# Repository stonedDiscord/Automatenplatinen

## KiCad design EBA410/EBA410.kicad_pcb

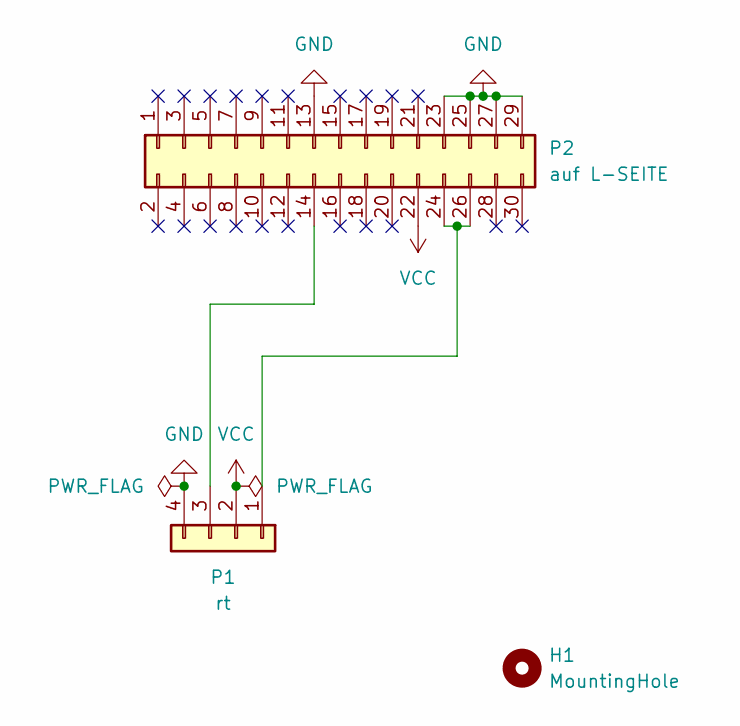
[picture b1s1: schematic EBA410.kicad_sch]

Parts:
H1: MountingHole; MountingHole_3.7mm
P1: rt; PinHeader_1x04_P2.54mm_Horizontal
P2: auf L-SEITE; PinHeader_2x15_P2.54mm_Vertical

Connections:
GND: P1.4, P2.13, P2.23, P2.25, P2.27, P2.29
unnamed: P1.1, P2.24, P2.26
unnamed: P1.3, P2.14
VCC: P1.2, P2.22

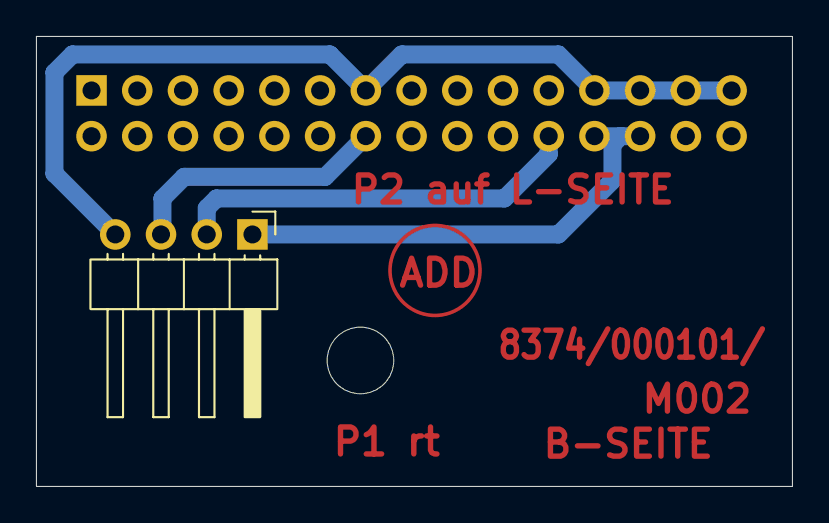
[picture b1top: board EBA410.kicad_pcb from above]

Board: 2 copper layers, 42.0 x 25.0 mm, 3 parts (1 on the bottom side), 4 nets.

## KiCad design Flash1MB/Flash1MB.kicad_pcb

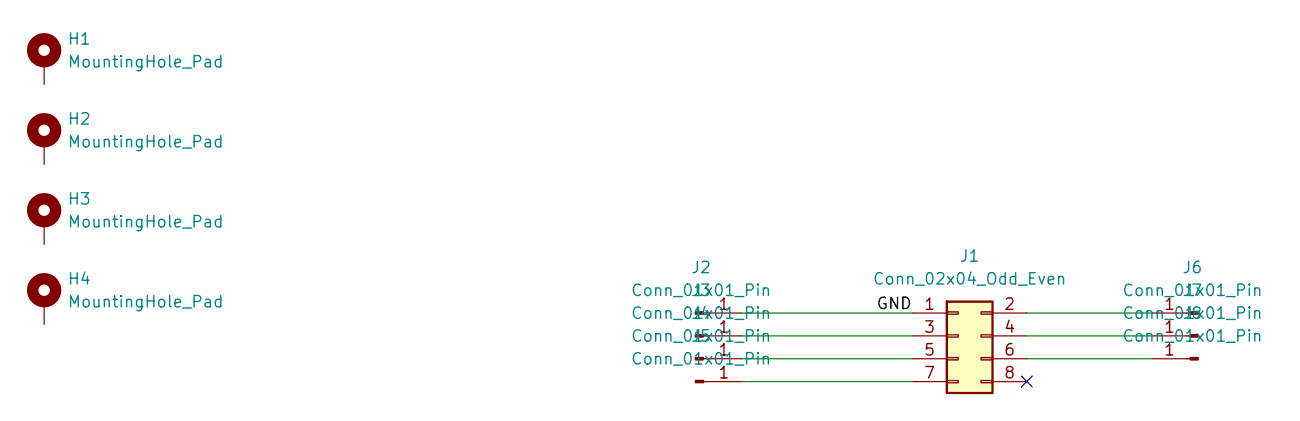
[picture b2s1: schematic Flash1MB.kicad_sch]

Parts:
H1, H2, H3, H4: MountingHole_Pad; MountingHole_2.2mm_M2_DIN965_Pad
J1: Conn_02x04_Odd_Even; PinHeader_2x04_P2.54mm_Vertical
J2, J3, J4, J5, J6, J7, J8: Conn_01x01_Pin; PinHeader_1x01_P2.54mm_Vertical

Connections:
/GND: J1.1, J2.1
unnamed: J1.2, J6.1
unnamed: J1.3, J3.1
unnamed: J1.4, J7.1
unnamed: J1.5, J4.1
unnamed: J1.6, J8.1
unnamed: J1.7, J5.1

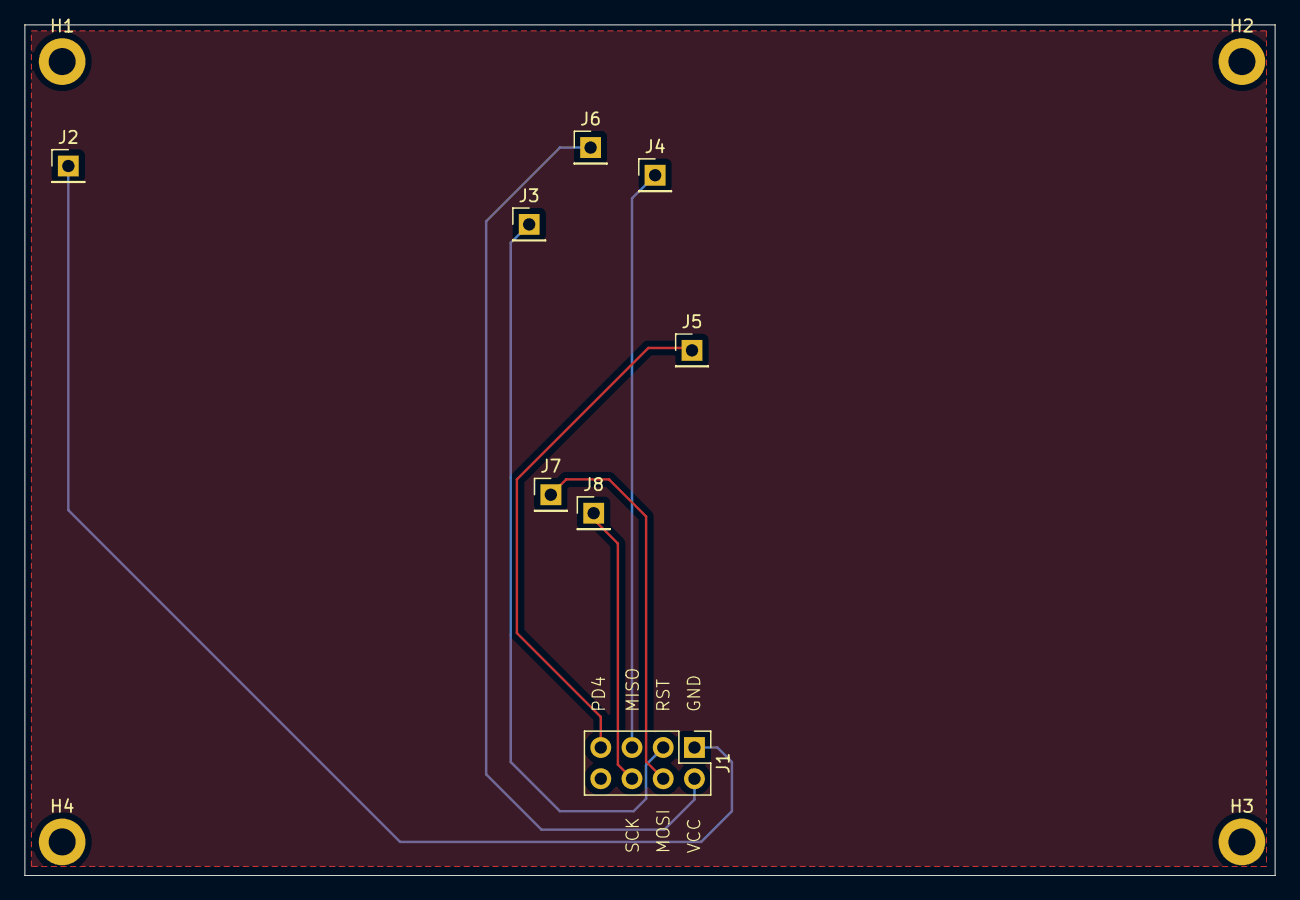
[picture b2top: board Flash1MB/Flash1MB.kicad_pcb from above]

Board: 2 copper layers, 101.7 x 69.2 mm, 12 parts (0 on the bottom side), 7 nets.

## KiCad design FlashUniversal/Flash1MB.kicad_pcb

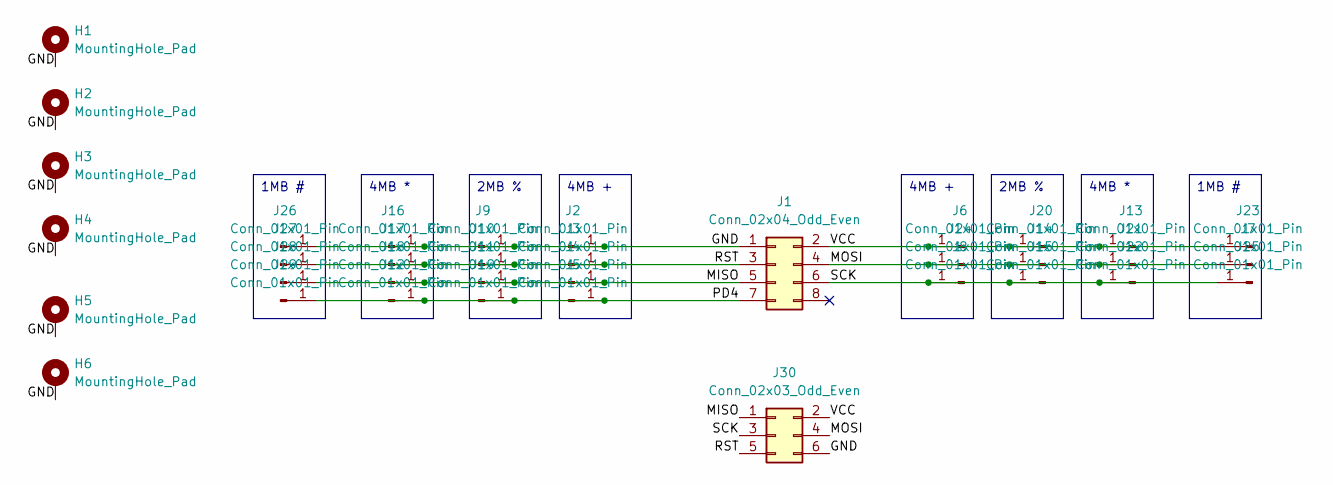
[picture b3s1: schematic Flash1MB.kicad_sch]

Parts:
H1, H2, H3, H4: MountingHole_Pad; MountingHole_4.3mm_M4_DIN965_Pad
H5, H6: MountingHole_Pad; MountingHole_2.2mm_M2_DIN965_Pad
J1: Conn_02x04_Odd_Even; PinHeader_2x04_P2.54mm_Vertical
J2, J3, J4, J5, J6, J7, J8, J9, J10, J11, J12, J13, J14, J15, J16, J17, J18, J19, J20, J21, J22, J23, J24, J25, J26, J27, J28, J29: Conn_01x01_Pin; PinHeader_1x01_P2.54mm_Vertical
J30: Conn_02x03_Odd_Even; PinHeader_2x03_P2.54mm_Vertical

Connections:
/GND: H1.1, H2.1, H3.1, H4.1, H5.1, H6.1, J1.1, J2.1, J9.1, J16.1, J26.1, J30.6
/MISO: J1.5, J4.1, J11.1, J18.1, J28.1, J30.1
/MOSI: J1.4, J7.1, J14.1, J21.1, J24.1, J30.4
/PD4: J1.7, J5.1, J12.1, J19.1, J29.1
/RST: J1.3, J3.1, J10.1, J17.1, J27.1, J30.5
/SCK: J1.6, J8.1, J15.1, J22.1, J25.1, J30.3
/VCC: J1.2, J6.1, J13.1, J20.1, J23.1, J30.2

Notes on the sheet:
4MB +
2MB %
1MB #
4MB *

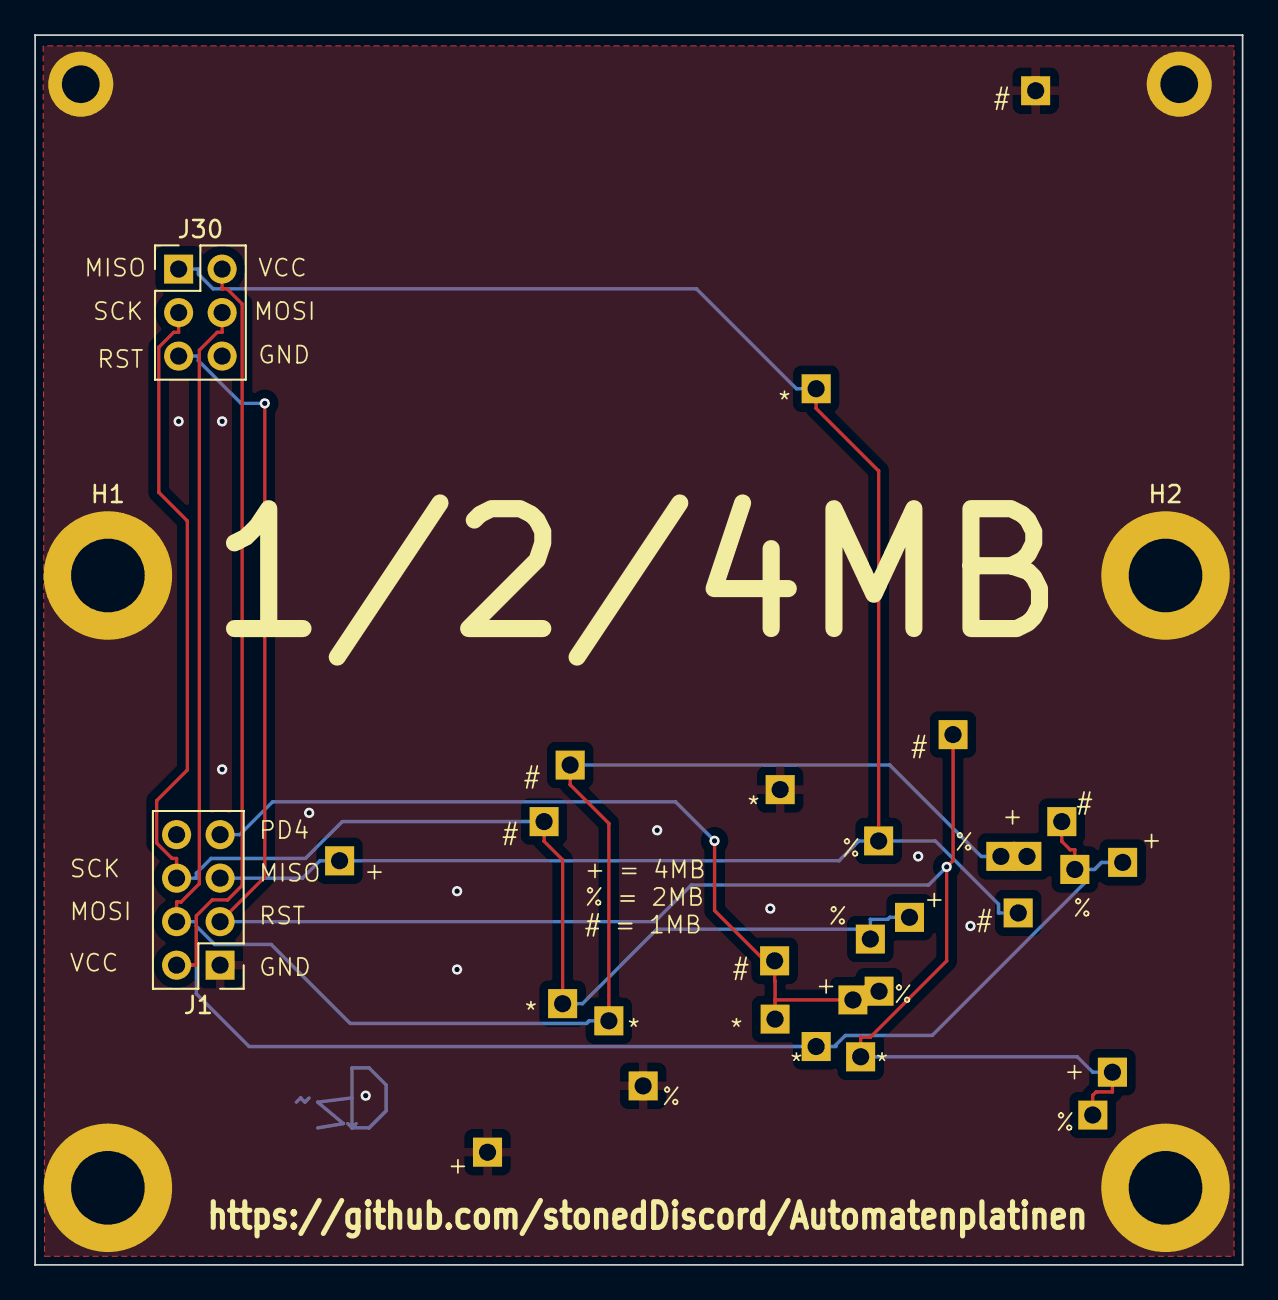
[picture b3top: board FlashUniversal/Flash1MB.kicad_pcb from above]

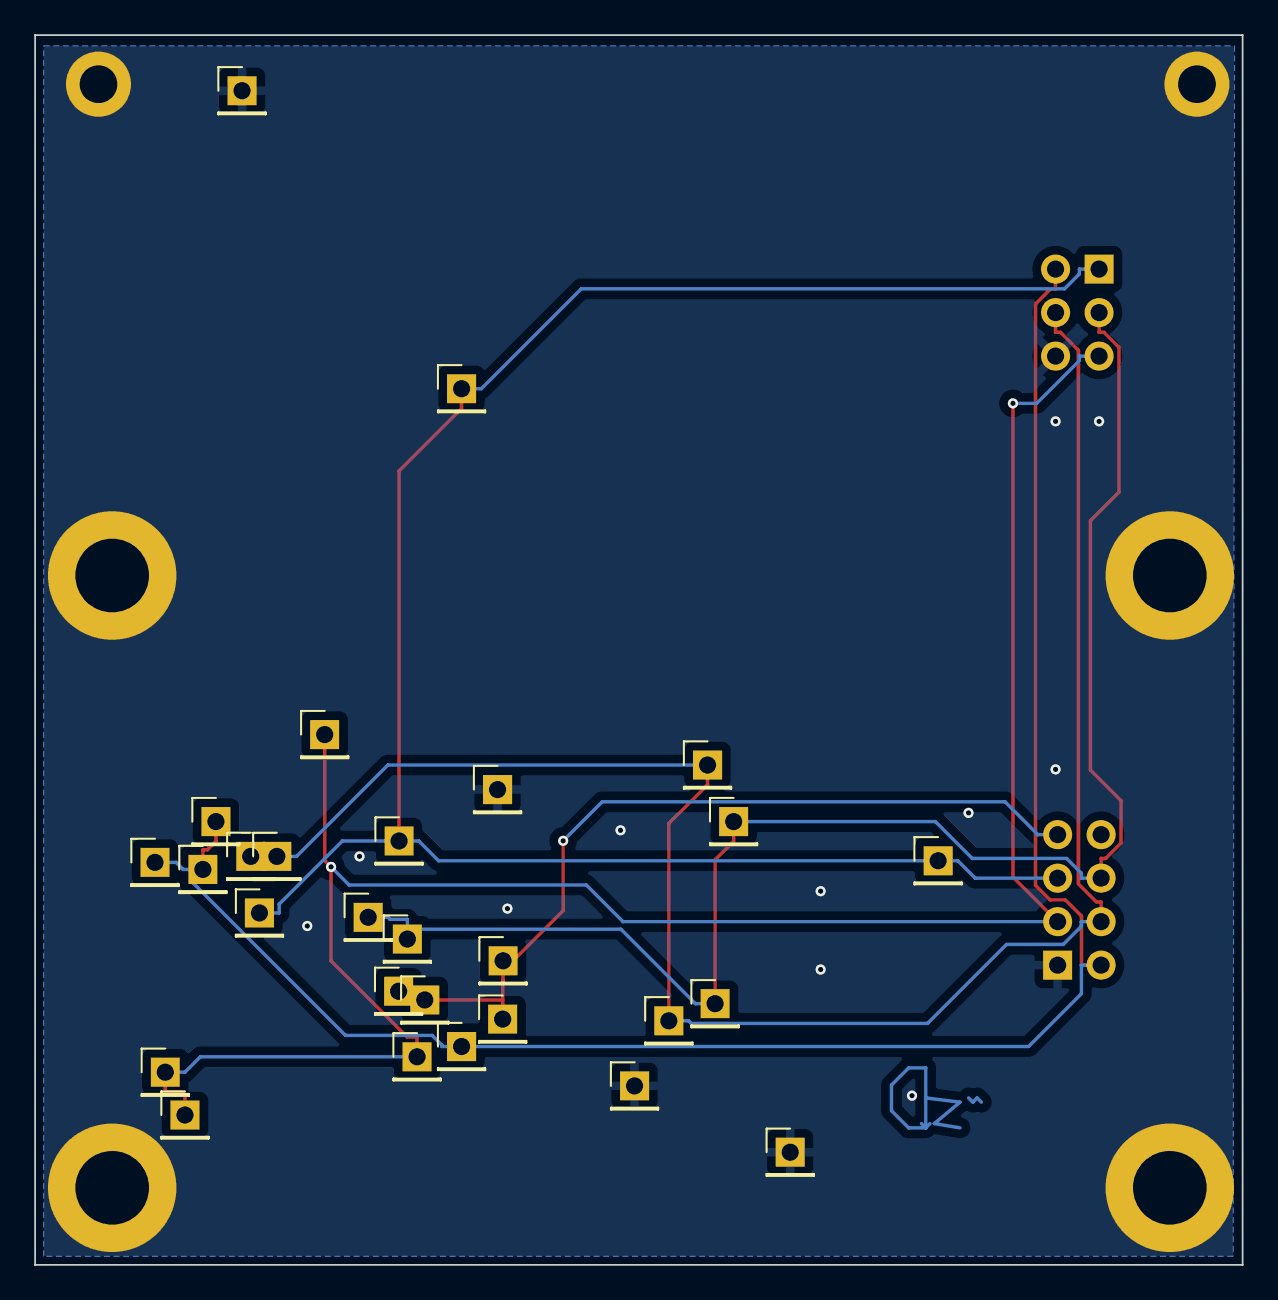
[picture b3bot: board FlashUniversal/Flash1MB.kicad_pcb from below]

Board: 2 copper layers, 70.5 x 71.8 mm, 36 parts (28 on the bottom side), 7 nets.

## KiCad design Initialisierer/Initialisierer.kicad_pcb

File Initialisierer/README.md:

# Initstecker
Stecker
https://aliexpress.com/item/4001198421663.html

Tasten
https://aliexpress.com/item/4000810443449.html

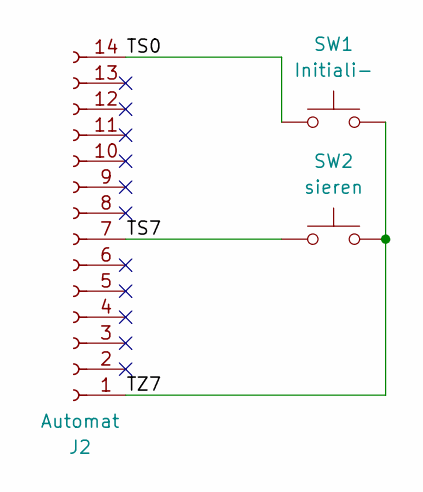
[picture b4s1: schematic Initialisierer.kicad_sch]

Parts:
J2: Automat; PinSocket_1x14_P2.54mm_Vertical
SW1: Initiali-; SW_SPST_CK_RS282G05A3
SW2: sieren; SW_SPST_CK_RS282G05A3

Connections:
/TS0: J2.14, SW1.1
/TS7: J2.7, SW2.1
/TZ7: J2.1, SW1.2, SW2.2

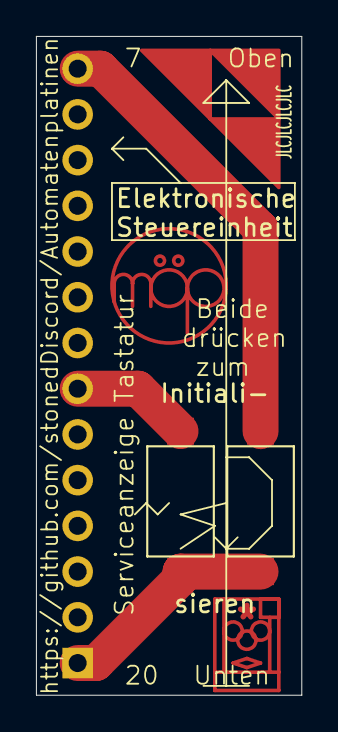
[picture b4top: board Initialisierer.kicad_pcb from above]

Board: 2 copper layers, 14.7 x 36.6 mm, 3 parts (1 on the bottom side), 3 nets.

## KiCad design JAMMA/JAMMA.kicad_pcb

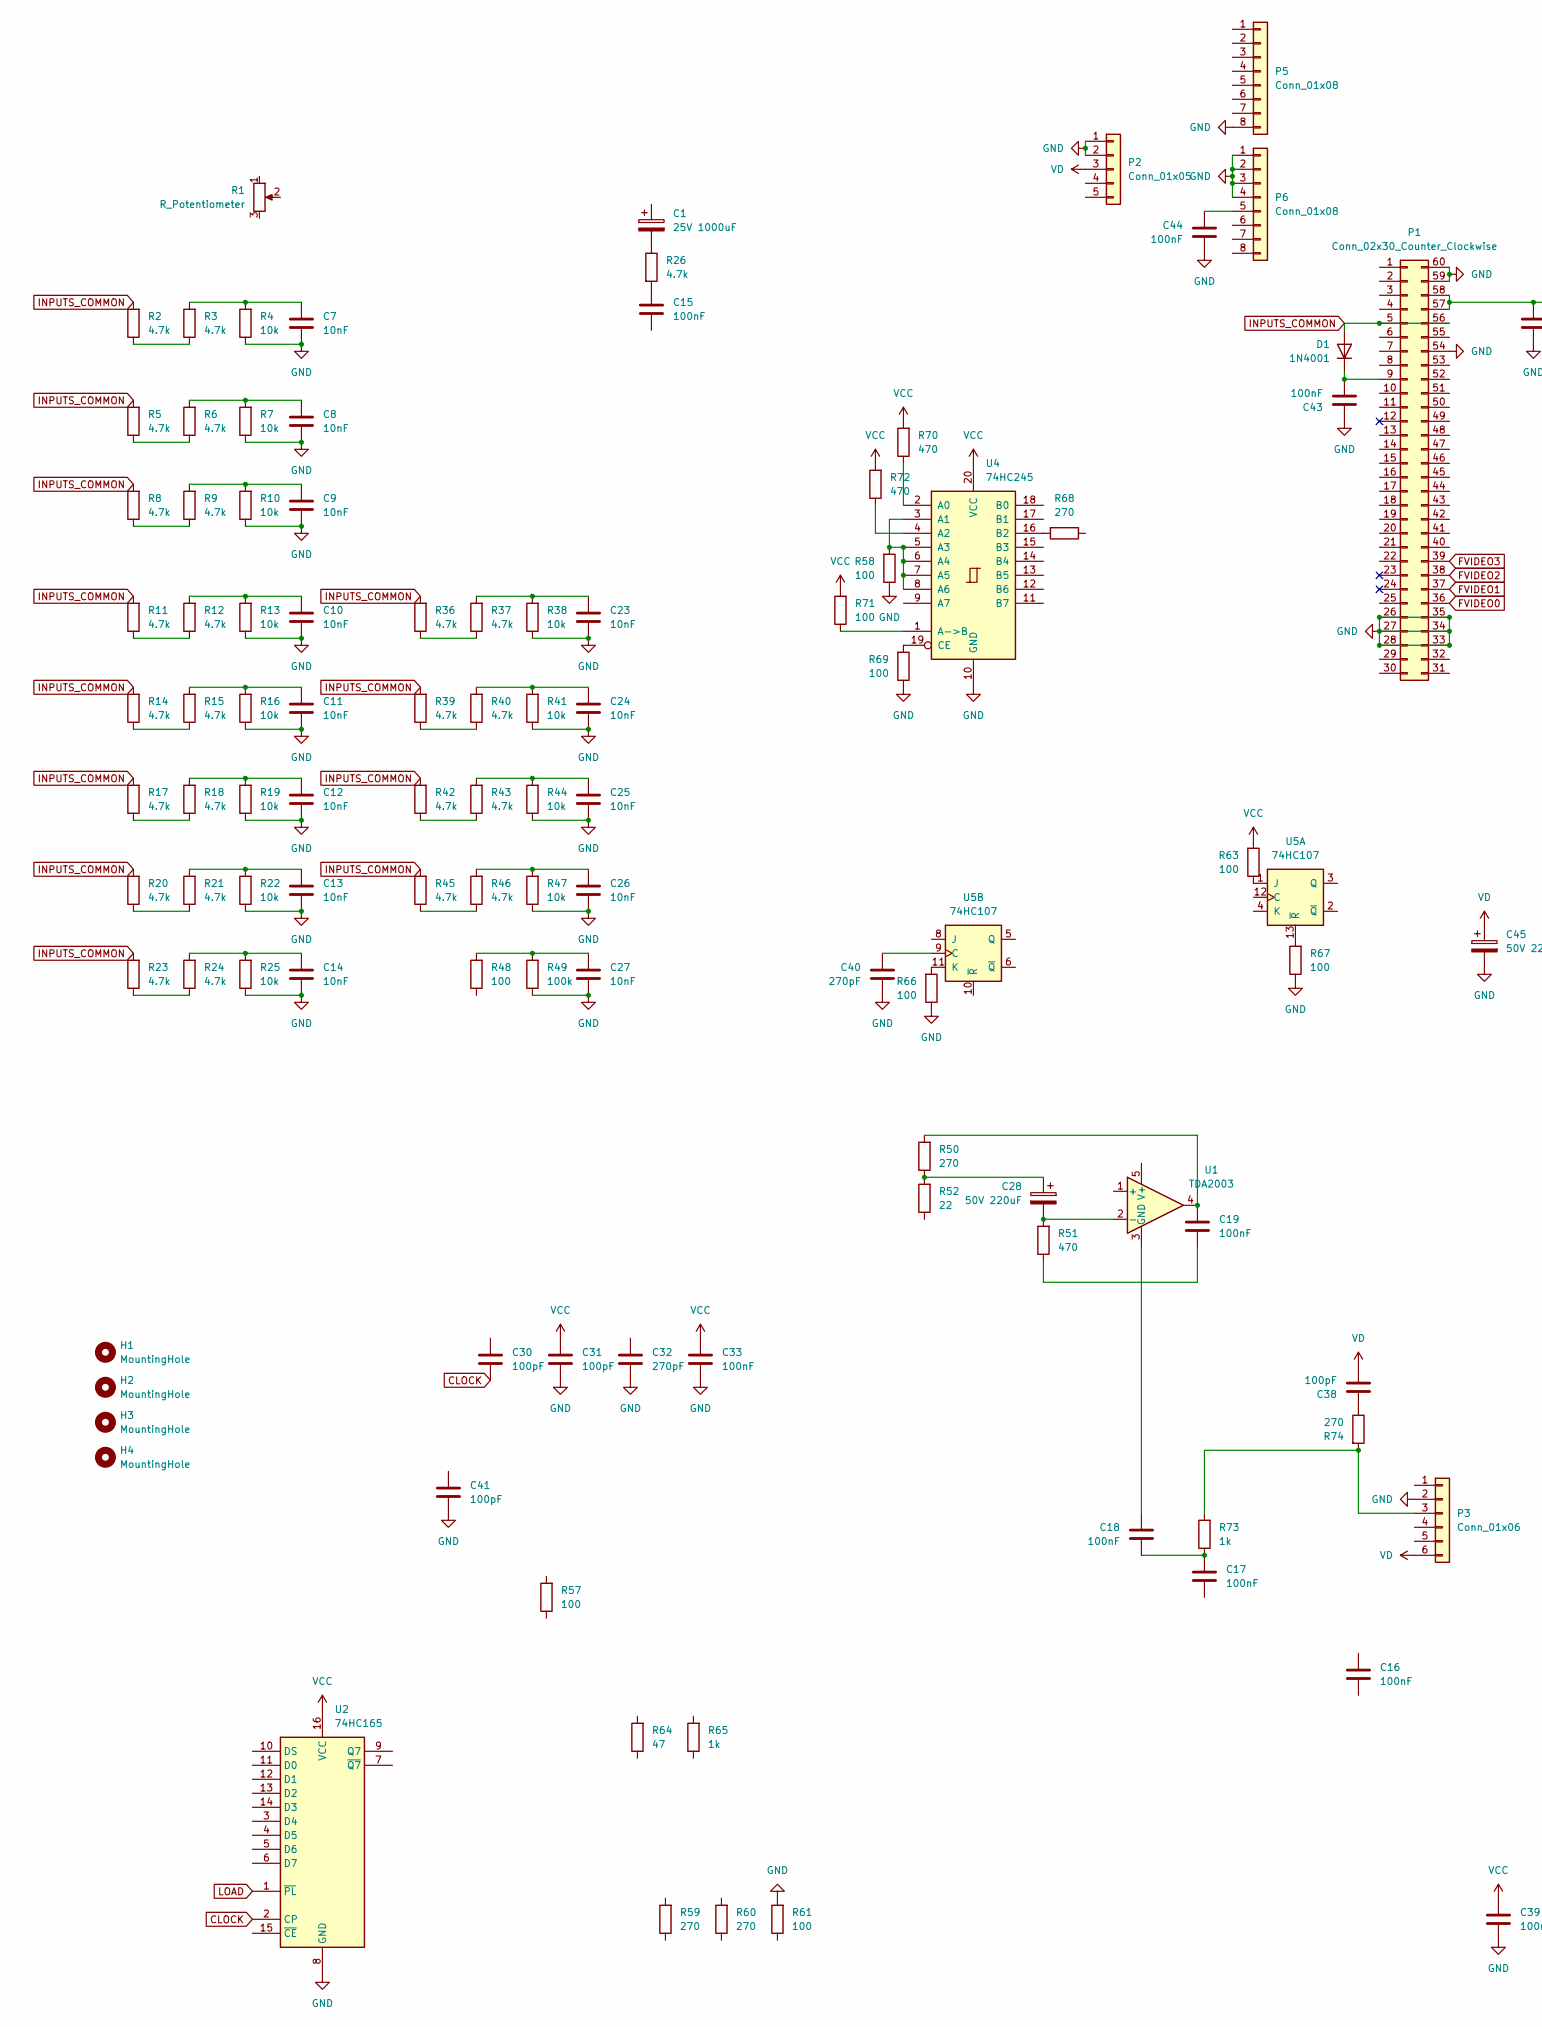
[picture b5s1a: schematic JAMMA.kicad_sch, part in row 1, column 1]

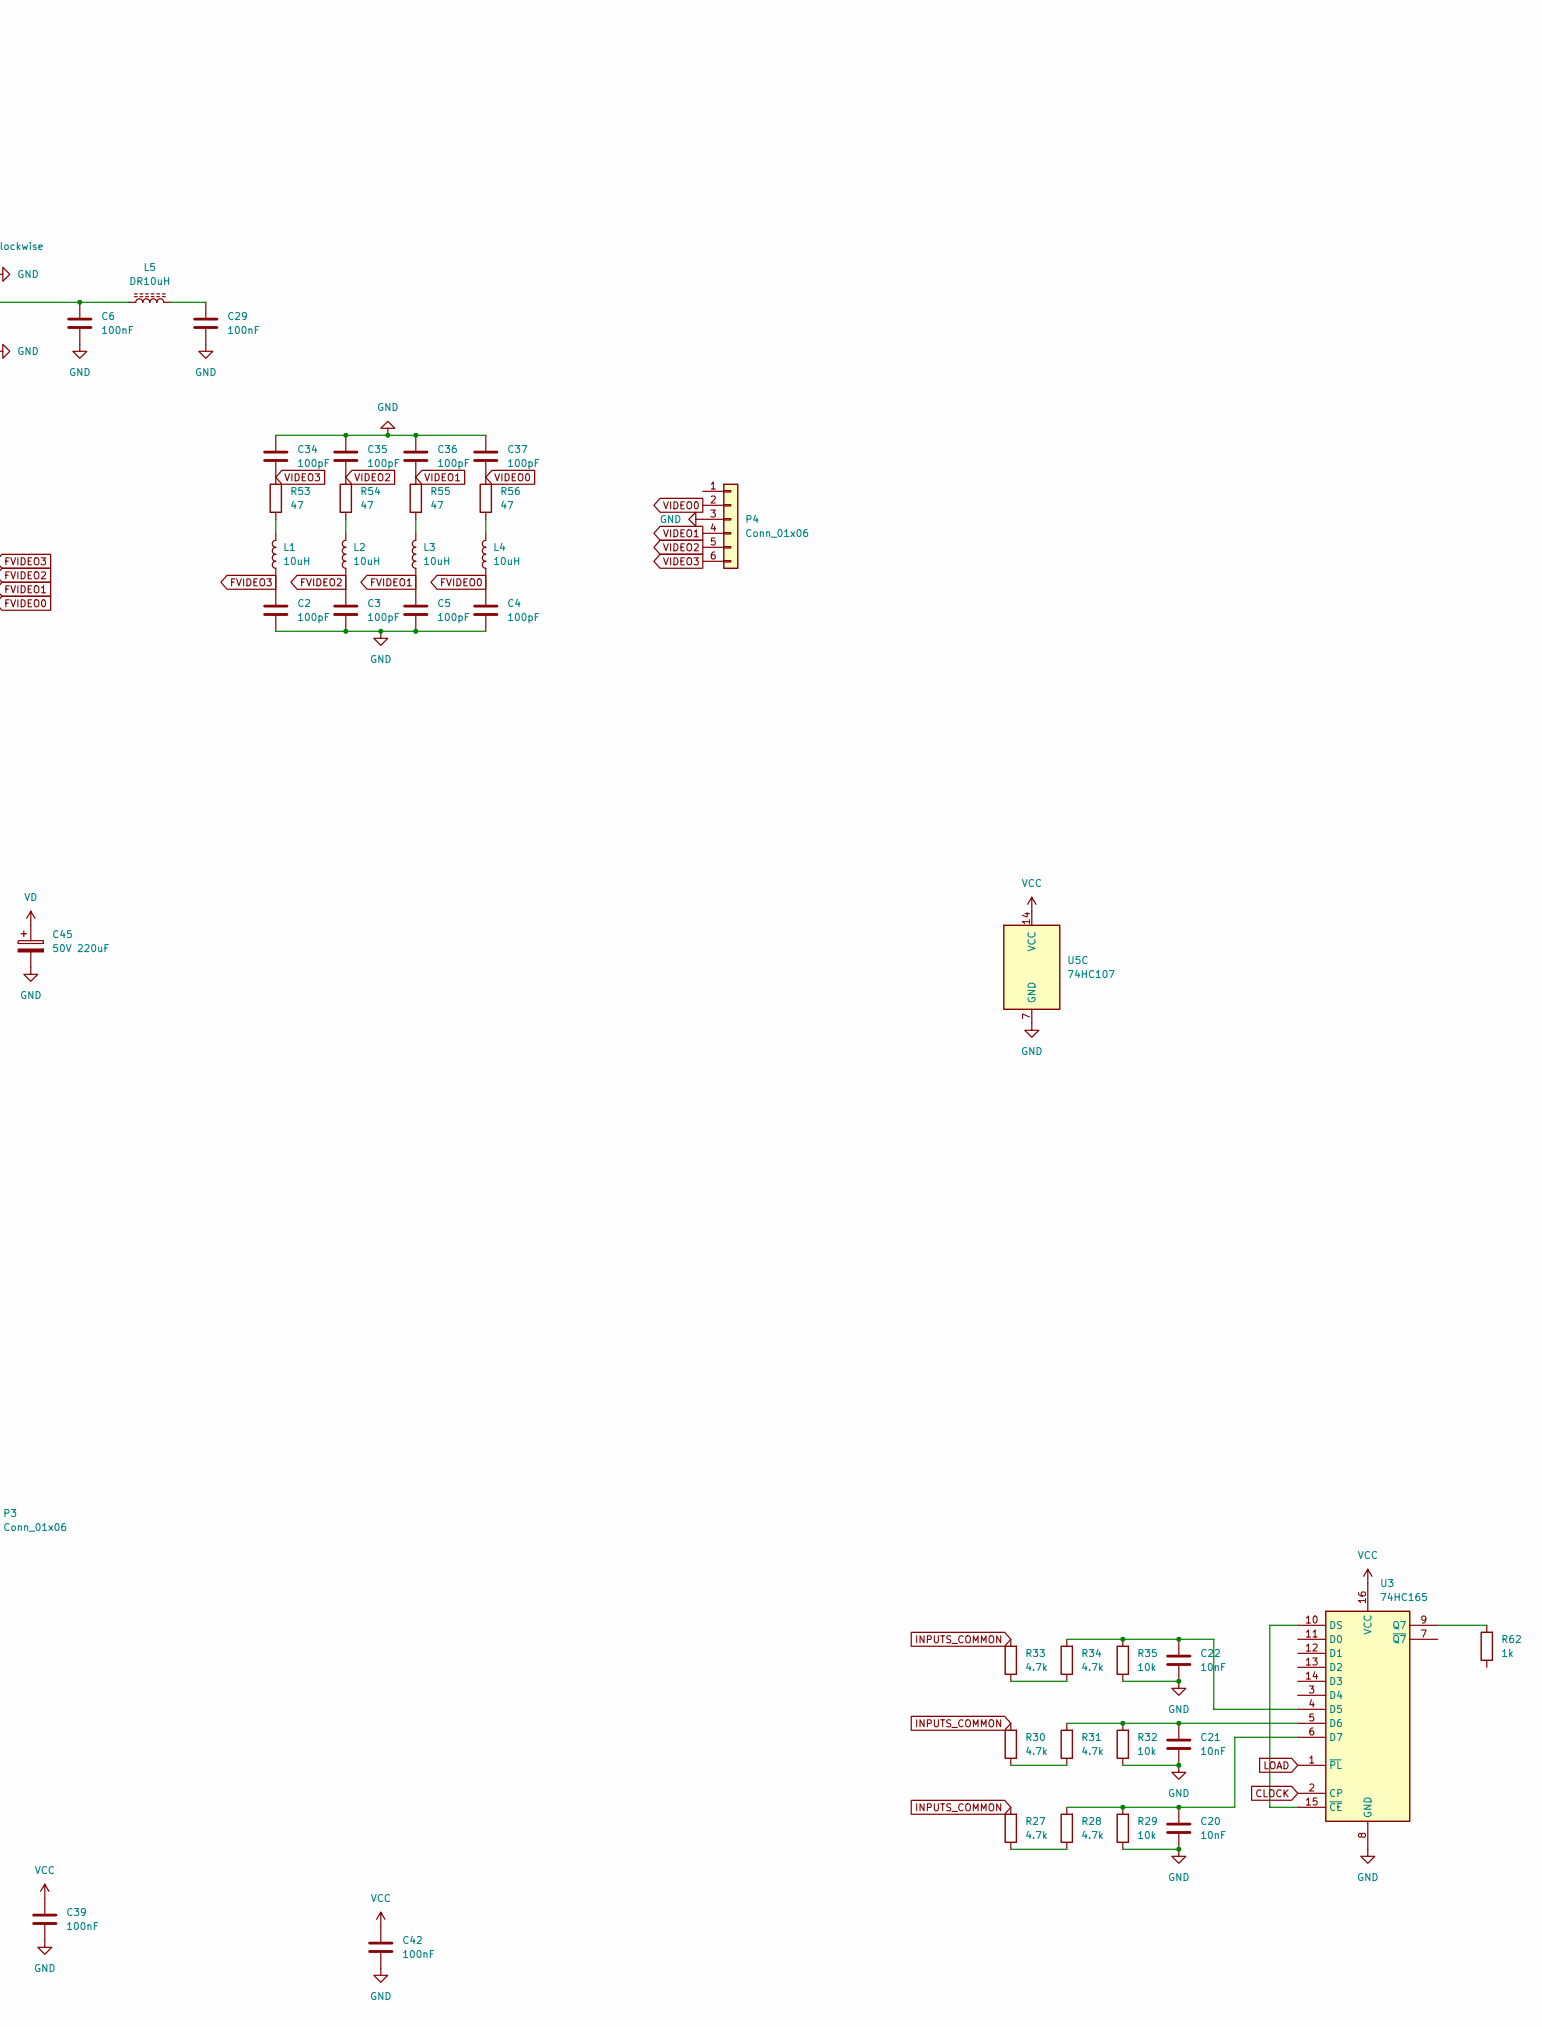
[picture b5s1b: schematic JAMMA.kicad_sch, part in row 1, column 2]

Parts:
C1: 25V 1000uF; CP_Axial_L29.0mm_D10.0mm_P35.00mm_Horizontal
C2, C3, C4, C5, C30, C31, C34, C35, C36, C37, C38, C41: 100pF; C_Axial_L3.8mm_D2.6mm_P7.50mm_Horizontal
C6, C15, C16, C17, C18, C19, C29, C33, C39, C42, C43, C44: 100nF; C_Axial_L3.8mm_D2.6mm_P7.50mm_Horizontal
C7, C8, C9, C10, C11, C12, C13, C14, C20, C21, C22, C23, C24, C25, C26, C27: 10nF; C_Axial_L3.8mm_D2.6mm_P7.50mm_Horizontal
C28, C45: 50V 220uF; CP_Radial_D8.0mm_P5.00mm
C32, C40: 270pF; C_Axial_L3.8mm_D2.6mm_P7.50mm_Horizontal
D1: 1N4001; D_DO-15_P15.24mm_Horizontal
H1, H2, H3, H4: MountingHole; MountingHole_3.7mm
L1, L2, L3, L4: 10uH; L_Axial_L7.0mm_D3.3mm_P12.70mm_Horizontal_Fastron_MICC
L5: DR10uH; L_Axial_L11.0mm_D4.5mm_P15.24mm_Horizontal_Fastron_MECC
P1: Conn_02x30_Counter_Clockwise; ADP_ARCADE
P2: Conn_01x05; Stocko_MKS_1655-6-0-505_1x5_P2.50mm_Vertical
P3, P4: Conn_01x06; Stocko_MKS_1656-6-0-606_1x6_P2.50mm_Vertical
P5, P6: Conn_01x08; Stocko_MKS_1658-6-0-808_1x8_P2.50mm_Vertical
R1: R_Potentiometer; Potentiometer_Piher_PT-15-V02_Vertical
R2, R3, R5, R6, R8, R9, R11, R12, R14, R15, R17, R18, R20, R21, R23, R24, R26, R27, R28, R30, R31, R33, R34, R36, R37, R39, R40, R42, R43, R45, R46: 4.7k; R_Axial_DIN0207_L6.3mm_D2.5mm_P10.16mm_Horizontal
R4, R7, R10, R13, R16, R19, R22, R25, R29, R32, R35, R38, R41, R44, R47: 10k; R_Axial_DIN0207_L6.3mm_D2.5mm_P10.16mm_Horizontal
R48, R57, R58, R61, R63, R66, R67, R69, R71: 100; R_Axial_DIN0207_L6.3mm_D2.5mm_P10.16mm_Horizontal
R49: 100k; R_Axial_DIN0207_L6.3mm_D2.5mm_P10.16mm_Horizontal
R50, R59, R60, R68, R74: 270; R_Axial_DIN0207_L6.3mm_D2.5mm_P10.16mm_Horizontal
R51, R70, R72: 470; R_Axial_DIN0207_L6.3mm_D2.5mm_P10.16mm_Horizontal
R52: 22; R_Axial_DIN0207_L6.3mm_D2.5mm_P10.16mm_Horizontal
R53, R54, R55, R56, R64: 47; R_Axial_DIN0207_L6.3mm_D2.5mm_P10.16mm_Horizontal
R62, R65, R73: 1k; R_Axial_DIN0207_L6.3mm_D2.5mm_P10.16mm_Horizontal
U1: TDA2003; TO-220-5_P3.4x3.8mm_StaggerOdd_Lead7.13mm_TabDown
U2, U3: 74HC165; DIP-16_W7.62mm
U4: 74HC245; DIP-20_W7.62mm
U5: 74HC107; DIP-14_W7.62mm

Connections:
CLOCK: C30.1, U2.2 (CP), U3.2 (CP)
FVIDEO0: C4.2, L4.1, P1.36
FVIDEO1: C5.2, L3.1, P1.37
FVIDEO2: C3.2, L2.1, P1.38
FVIDEO3: C2.2, L1.1, P1.39
GND: C2.1, C3.1, C4.1, C5.1, C6.2, C7.1, C8.1, C9.1, C10.1, C11.1, C12.1, C13.1, C14.1, C20.1, C21.1, C22.1, C23.1, C24.1, C25.1, C26.1, C27.1, C29.2, C31.1, C32.1, C33.1, C34.1, C35.1, C36.1, C37.1, C39.1, C40.1, C41.1, C42.1, C43.2, C44.1, C45.2, P1.26, P1.27, P1.28, P1.33, P1.34, P1.35, P1.54, P1.59, P1.60, P2.1, P2.2, P3.2, P4.3, P5.8 (Pin_8_8), P6.1, P6.2, P6.3, P6.4, R4.1, R7.1, R10.1, R13.1, R16.1, R19.1, R22.1, R25.1, R29.1, R32.1, R35.1, R38.1, R41.1, R44.1, R47.1, R49.1, R58.1, R61.2, R66.1, R67.1, R69.1, U2.8 (GND), U3.8 (GND), U4.10 (GND), U5.7 (GND)
INPUTS_COMMON: D1.2 (A), P1.5, P1.56, R2.2, R5.2, R8.2, R11.2, R14.2, R17.2, R20.2, R23.2, R27.2, R30.2, R33.2, R36.2, R39.2, R42.2, R45.2
LOAD: U2.1 (~PL), U3.1 (~PL)
unnamed: C1.2, R26.1
unnamed: C7.2, R3.2, R4.2
unnamed: C8.2, R6.2, R7.2
unnamed: C9.2, R9.2, R10.2
unnamed: C10.2, R12.2, R13.2
unnamed: C11.2, R15.2, R16.2
unnamed: C12.2, R18.2, R19.2
unnamed: C13.2, R21.2, R22.2
unnamed: C14.2, R24.2, R25.2
unnamed: C15.2, R26.2
unnamed: C17.2, C18.1, R73.1
unnamed: C19.1, R51.1
unnamed: C19.2, R50.2, U1.4
unnamed: C23.2, R37.2, R38.2
unnamed: C24.2, R40.2, R41.2
unnamed: C25.2, R43.2, R44.2
unnamed: C26.2, R46.2, R47.2
unnamed: C27.2, R48.2, R49.2
unnamed: C28.1, R50.1, R52.2
unnamed: C29.1, L5.2
unnamed: C38.2, R74.1
unnamed: C43.1, D1.1 (K), P1.9
unnamed: L1.2, R53.1
unnamed: L2.2, R54.1
unnamed: L3.2, R55.1
unnamed: L4.2, R56.1
unnamed: C6.1, L5.1, P1.57, P1.58
unnamed: P3.3, R73.2, R74.2
unnamed: C44.2, P6.5
unnamed: R2.1, R3.1
unnamed: R5.1, R6.1
unnamed: R8.1, R9.1
unnamed: R11.1, R12.1
unnamed: R14.1, R15.1
unnamed: R17.1, R18.1
unnamed: R20.1, R21.1
unnamed: R23.1, R24.1
unnamed: R27.1, R28.1
unnamed: R30.1, R31.1
unnamed: R33.1, R34.1
unnamed: R36.1, R37.1
unnamed: R39.1, R40.1
unnamed: R42.1, R43.1
unnamed: R45.1, R46.1
unnamed: C28.2, R51.2, U1.2 (-)
unnamed: C18.2, U1.3 (GND)
unnamed: C22.2, R34.2, R35.2, U3.4 (D5)
unnamed: C21.2, R31.2, R32.2, U3.5 (D6)
unnamed: C20.2, R28.2, R29.2, U3.6 (D7)
unnamed: U3.10 (DS), U3.15 (~CE)
unnamed: R62.2, U3.9 (Q7)
unnamed: R70.1, U4.2 (A0)
unnamed: R58.2, U4.3 (A1), U4.5 (A3), U4.6 (A4), U4.7 (A5), U4.8 (A6)
unnamed: R72.1, U4.4 (A2)
unnamed: R71.1, U4.1 (A->B)
unnamed: R68.2, U4.16 (B2)
unnamed: R69.2, U4.19 (CE)
unnamed: R63.1, U5.1 (J)
unnamed: R67.2, U5.13 (~R)
unnamed: C40.2, U5.9 (C)
unnamed: R66.2, U5.11 (K)
VCC: C31.2, C33.2, C39.2, C42.2, R63.2, R70.2, R71.2, R72.2, U2.16 (VCC), U3.16 (VCC), U4.20 (VCC), U5.14 (VCC)
VD: C38.1, C45.1, P2.3, P3.6
VIDEO0: C37.2, P4.2, R56.2
VIDEO1: C36.2, P4.4, R55.2
VIDEO2: C35.2, P4.5, R54.2
VIDEO3: C34.2, P4.6, R53.2

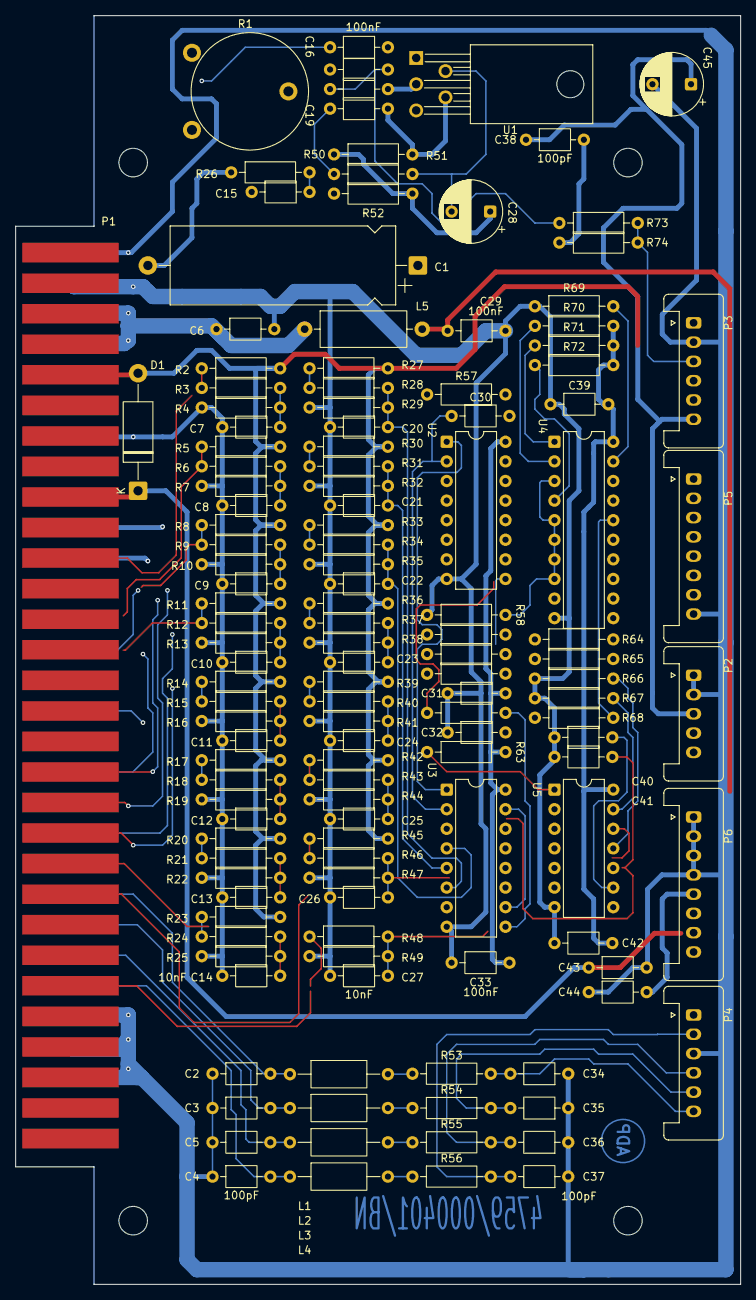
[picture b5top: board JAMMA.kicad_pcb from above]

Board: 2 copper layers, 94.0 x 164.5 mm, 140 parts (0 on the bottom side), 75 nets.
